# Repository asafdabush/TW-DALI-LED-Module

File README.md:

# TW DALI LED Module: Two-Channel Tunable-White Driver with Isolated DALI Interface

A Ø50 mm round control-and-driver module for tunable-white (TW) COB LEDs. It takes a 24 V constant-voltage supply, drives a warm and a cool LED channel with independent constant-current buck regulators, and is controlled over an optically isolated DALI bus by an STM32G0 microcontroller.

Personal hardware project, designed end to end in KiCad 9.

**Status:** schematic and 2-layer layout complete. Next steps are fabrication, bring-up and the DALI DT8 firmware.

---

Full schematic: [`docs/schematic.pdf`](docs/schematic.pdf)

## Architecture

```mermaid
flowchart LR
    V[24 V CV input] --> P[Protection<br/>SS34 reverse-polarity<br/>1.1 A PTC · SMBJ26A TVS]
    P --> REG[L78L33<br/>3.3 V]
    P --> CW[AL8860 buck<br/>cool channel]
    P --> WW[AL8860 buck<br/>warm channel]
    REG --> MCU[STM32G071KB]
    MCU -- PWM / DAC --> CW
    MCU -- PWM / DAC --> WW
    CW --> LC[COB cool]
    WW --> LW[COB warm]
    BUS[DALI bus] --- ISO[Isolated DALI PHY<br/>2× TCMT1107 opto]
    ISO -- RX / TX --> MCU
```

The board is split into two galvanically isolated domains: the 24 V power and MCU domain, and the DALI bus domain. The only link between them is the two optocouplers (3.75 kV rms).

## Design Blocks

### Power input

- **Reverse-polarity protection:** SS34 Schottky in series.
- **Overcurrent:** 1.1 A resettable PTC fuse.
- **Transient clamp:** SMBJ26A TVS across the 24 V rail.
- **Logic supply:** L78L33 linear regulator for the MCU only, so its dissipation stays small (≈ 20.7 V × ~10 mA ≈ 0.2 W).

### Constant-current LED channels (×2, one hierarchical sheet instantiated twice)

- **Topology:** AL8860 hysteretic buck with high-side current sensing, a 47 µH Bourns SRN6028 inductor and a PMEG4010 freewheel Schottky.
- **Output current:** set by the sense resistor, I_LED = V_SENSE / R_S = 0.1 V / 0.15 Ω ≈ **667 mA** per channel (nominal), with P_RS ≈ 67 mW.
- **Dimming:** the CTRL pin accepts either timer PWM directly, or an analog level from the MCU DAC through 1 kΩ. Firmware keeps whichever source is unused in high impedance. A 10 kΩ pull-down holds the LEDs off while the MCU is in reset.
- **Decoupling:** 4.7 µF + 100 nF / 50 V at each regulator input.

### Isolated DALI physical layer

- **Polarity-free bus connection:** MB6S bridge rectifier, with an SMBJ24A TVS across the bus.
- **Receive:** a BZX384-C5V1 Zener sets the detection threshold between DALI low (< 4.5 V) and high (> 9.5 V). The opto LED current is limited by a two-transistor current sink (BC847 pair, R = 680 Ω), so I ≈ V_BE / R ≈ 1 mA, inside the DALI 2 mA per-device budget. The receiver output is pulled up to 3.3 V, so the logic is inverted (bus idle-high gives RX low).
- **Transmit:** the MCU drives the TCMT1107 LED through 330 Ω (≈ 6 mA). The opto output pulls the gate of an AO3400A to the bus through 10 kΩ, and the MOSFET shorts the rectified bus to signal a logic low. A 10 V Zener clamps V_GS, and 100 kΩ keeps the gate off by default.

### Microcontroller

| Function | STM32G071KB pin |
|---|---|
| DALI RX / TX | PA0 / PA1 |
| PWM cool / warm | PA6 (TIM3_CH1) / PA3 (TIM2_CH4) |
| DAC cool / warm | PA5 (DAC1_OUT2) / PA4 (DAC1_OUT1) |
| Programming | SWD test pads: 3V3, SWDIO, SWCLK, NRST, GND |

## PCB

- Round Ø50 mm, 2 layers, 1.6 mm FR-4, two M3 mounting holes.
- An isolation barrier: a ~5 mm copper keep-out band across the board under the two optocouplers separates the 24 V/MCU domain from the DALI domain. The bottom-layer ground pour stays on the power side only.
- Wide traces (0.8 mm `Power` net class) for the 24 V rail and the LED current loops. The buck switching loops are kept tight around each AL8860, its inductor and its freewheel diode.
- Solder-wire pads for 24 V in, DALI, and the two COB channels.

## Repository Contents

| Path | Contents |
|---|---|
| [`docs/schematic.pdf`](docs/schematic.pdf) | Full schematic, 6 sheets |
| [`hardware/`](hardware) | KiCad 9 project: root sheet plus `power`, `led_channel` (×2), `mcu` and `dali` sub-sheets, and the PCB |
| [`docs/BOM.csv`](docs/BOM.csv) | Bill of materials (47 parts, 31 lines) |
| [`docs/pcb_top.png`](docs/pcb_top.png) | Layout render |

Open `hardware/TW_DALI_Module.kicad_pro` in KiCad 9 or later.

## Roadmap

- [ ] Fabricate and assemble the first batch
- [ ] Bring-up: verify 3.3 V rail, set-current accuracy, buck ripple and switching frequency at 24 V
- [ ] DALI PHY: verify the RX threshold and the TX timing (1200 bit/s Manchester) with a DALI master. The estimated bus-side threshold (Zener + opto LED + V_BE + bridge drops) is ≈ 8.5–9 V, so the margin to the 9.5 V high level needs to be measured
- [ ] Firmware: IEC 62386-102 control gear plus DT8 colour-temperature commands
- [ ] Thermal measurement at full load on both channels

## License

[CERN Open Hardware Licence v2 – Strongly Reciprocal](LICENSE)

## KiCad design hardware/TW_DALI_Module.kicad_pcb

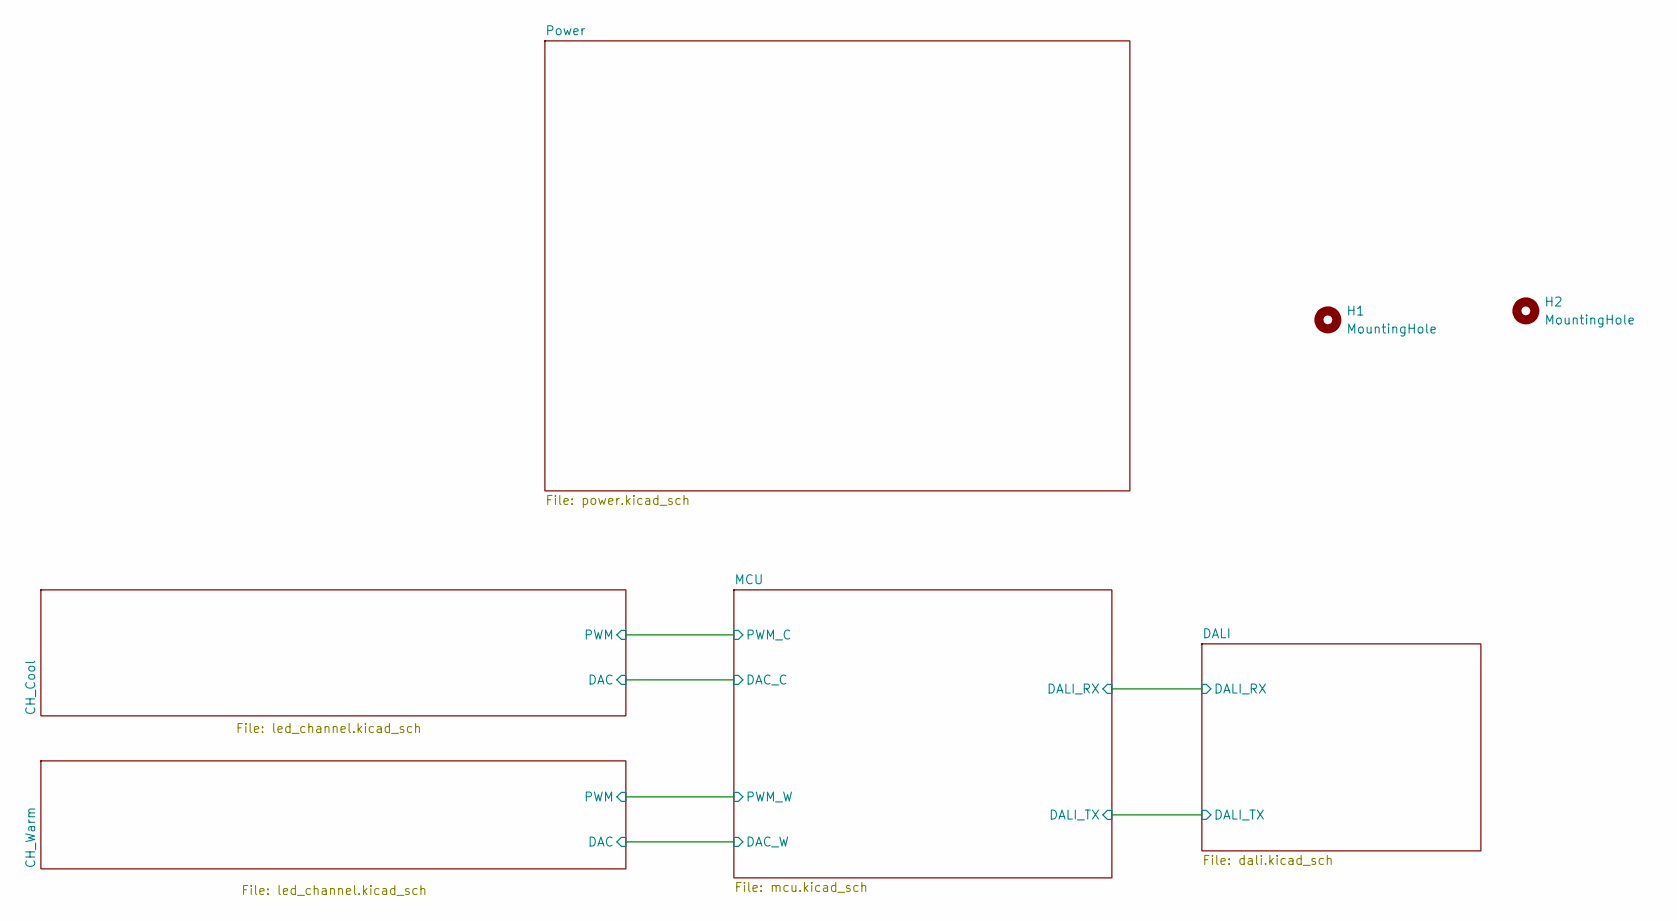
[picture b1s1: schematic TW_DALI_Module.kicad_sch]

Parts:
H1, H2: MountingHole; MountingHole_3.2mm_M3

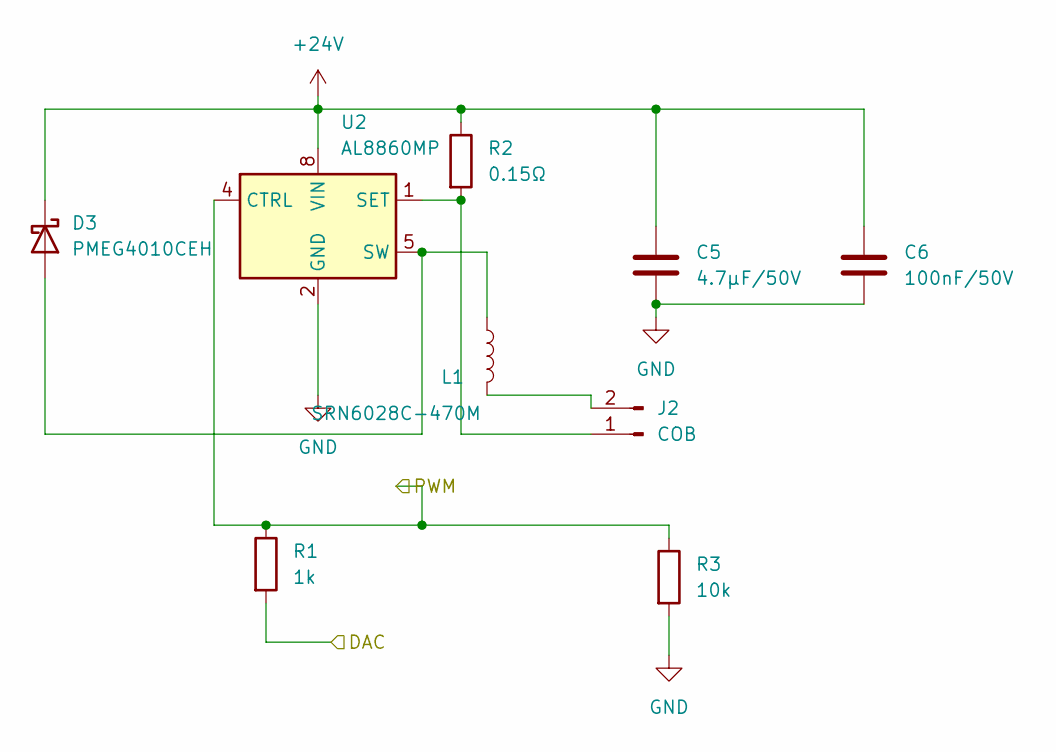
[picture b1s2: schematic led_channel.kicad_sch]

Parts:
C5: 4.7µF/50V; C_1206_3216Metric
C6: 100nF/50V; C_0603_1608Metric
D3: PMEG4010CEH; D_SOD-123F
J2: COB; SolderWire-0.5sqmm_1x02_P4.6mm_D0.9mm_OD2.1mm
L1: SRN6028C-470M; L_Bourns-SRN6028
R1: 1k; R_0603_1608Metric
R2: 0.15Ω; R_0805_2012Metric
R3: 10k; R_0603_1608Metric
U2: AL8860MP; MSOP-8-1EP_3x3mm_P0.65mm_EP1.5x1.8mm

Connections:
+24V: C5.1, C6.1, D3.1 (K), R2.1, U2.8 (VIN); also elsewhere on the board
/CH_Cool/DAC: R1.2; also elsewhere on the board
/CH_Cool/PWM: R1.1, R3.1, U2.4 (CTRL); also elsewhere on the board
GND: C5.2, C6.2, R3.2, U2.2 (GND), U2.3 (GND), U2.9 (GND); also elsewhere on the board
unnamed: D3.2 (A), L1.1, U2.5 (SW), U2.6 (SW)
unnamed: J2.1, R2.2, U2.1 (SET)
unnamed: J2.2, L1.2

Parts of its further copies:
C7: 4.7µF/50V; C_1206_3216Metric
C8: 100nF/50V; C_0603_1608Metric
D4: PMEG4010CEH; D_SOD-123F
J3: COB; SolderWire-0.5sqmm_1x02_P4.6mm_D0.9mm_OD2.1mm
L2: SRN6028C-470M; L_Bourns-SRN6028
R4: 1k; R_0603_1608Metric
R5: 0.15Ω; R_0805_2012Metric
R6: 10k; R_0603_1608Metric
U3: AL8860MP; MSOP-8-1EP_3x3mm_P0.65mm_EP1.5x1.8mm

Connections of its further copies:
+24V: C7.1, C8.1, D4.1 (K), R5.1, U3.8 (VIN); also elsewhere on the board
/CH_Warm/DAC: R4.2; also elsewhere on the board
/CH_Warm/PWM: R4.1, R6.1, U3.4 (CTRL); also elsewhere on the board
GND: C7.2, C8.2, R6.2, U3.2 (GND), U3.3 (GND), U3.9 (GND); also elsewhere on the board
unnamed: D4.2 (A), L2.1, U3.5 (SW), U3.6 (SW)
unnamed: J3.1, R5.2, U3.1 (SET)
unnamed: J3.2, L2.2

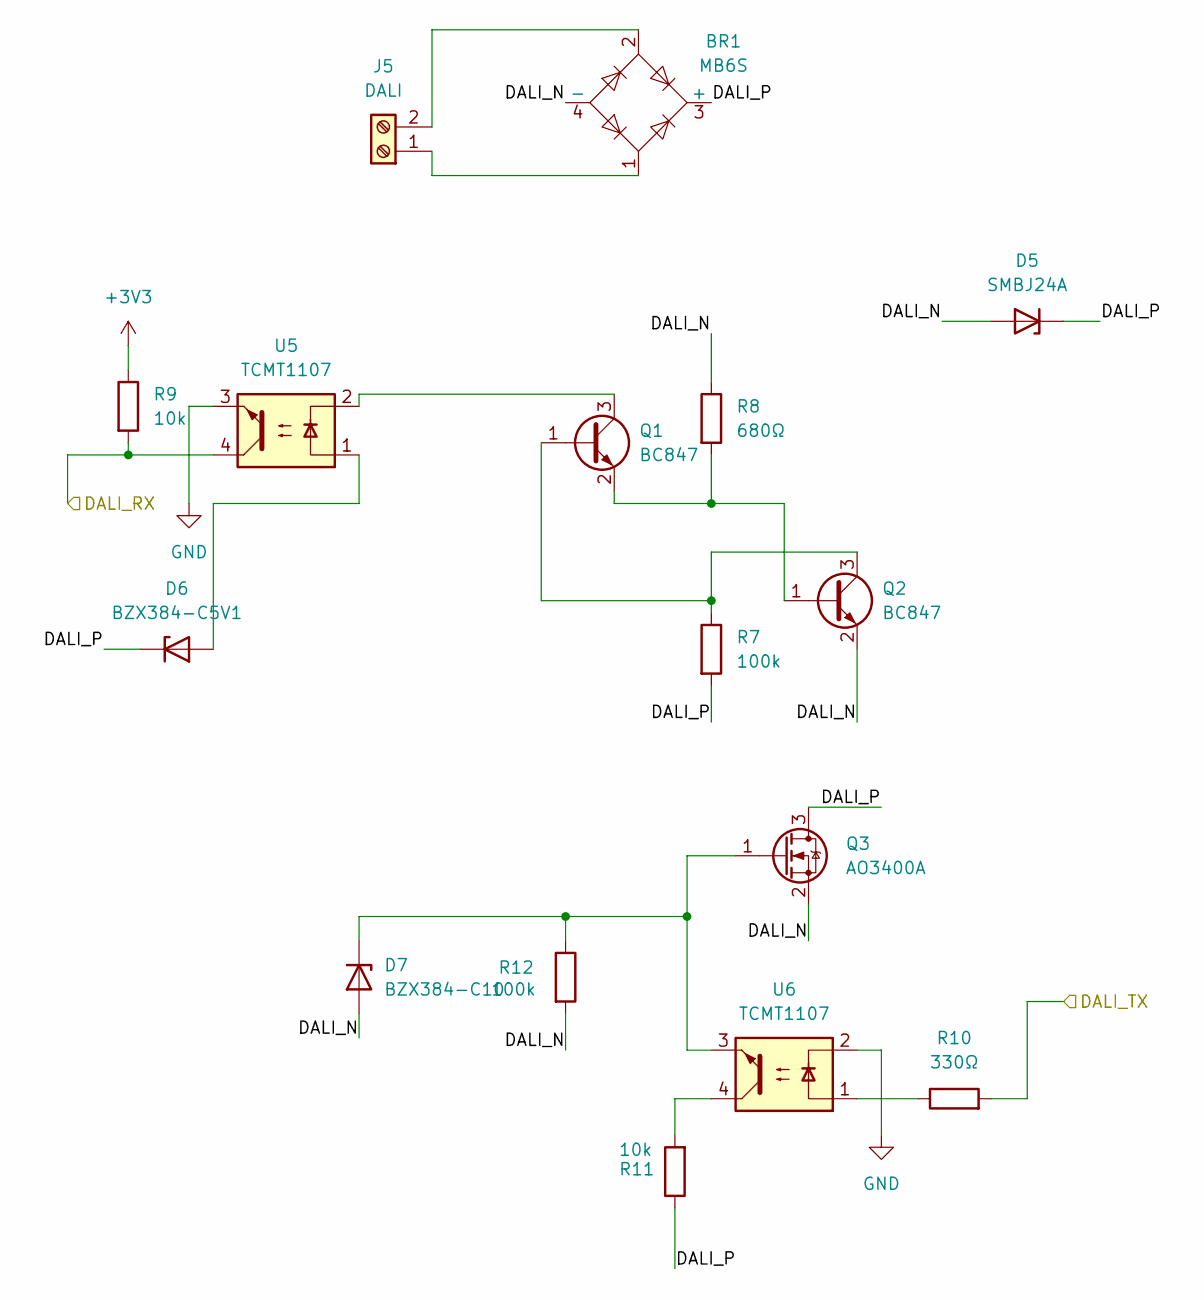
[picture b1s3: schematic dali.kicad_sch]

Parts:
BR1: MB6S; TO-269AA
D5: SMBJ24A; D_SMB
D6: BZX384-C5V1; D_SOD-323
D7: BZX384-C10; D_SOD-323
J5: DALI; SolderWire-0.5sqmm_1x02_P4.6mm_D0.9mm_OD2.1mm
Q1, Q2: BC847; SOT-23
Q3: AO3400A; SOT-23
R7, R12: 100k; R_0603_1608Metric
R8: 680Ω; R_0603_1608Metric
R9, R11: 10k; R_0603_1608Metric
R10: 330Ω; R_0603_1608Metric
U5, U6: TCMT1107; SOP-4_4.4x2.6mm_P1.27mm

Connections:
+3V3: R9.1; also elsewhere on the board
/DALI/DALI_N: BR1.4 (-), D5.2 (A), D7.2 (A), Q2.2 (E), Q3.2 (S), R8.1, R12.2
/DALI/DALI_P: BR1.3 (+), D5.1 (K), D6.1 (K), Q3.3 (D), R7.2, R11.1
/DALI/DALI_RX: R9.2, U5.4; also elsewhere on the board
/DALI/DALI_TX: R10.2; also elsewhere on the board
GND: U5.3, U6.2; also elsewhere on the board
unnamed: D6.2 (A), U5.1
unnamed: D7.1 (K), Q3.1 (G), R12.1, U6.3
unnamed: BR1.1, J5.1
unnamed: BR1.2, J5.2
unnamed: Q1.1 (B), Q2.3 (C), R7.1
unnamed: Q1.3 (C), U5.2
unnamed: Q1.2 (E), Q2.1 (B), R8.2
unnamed: R10.1, U6.1
unnamed: R11.2, U6.4

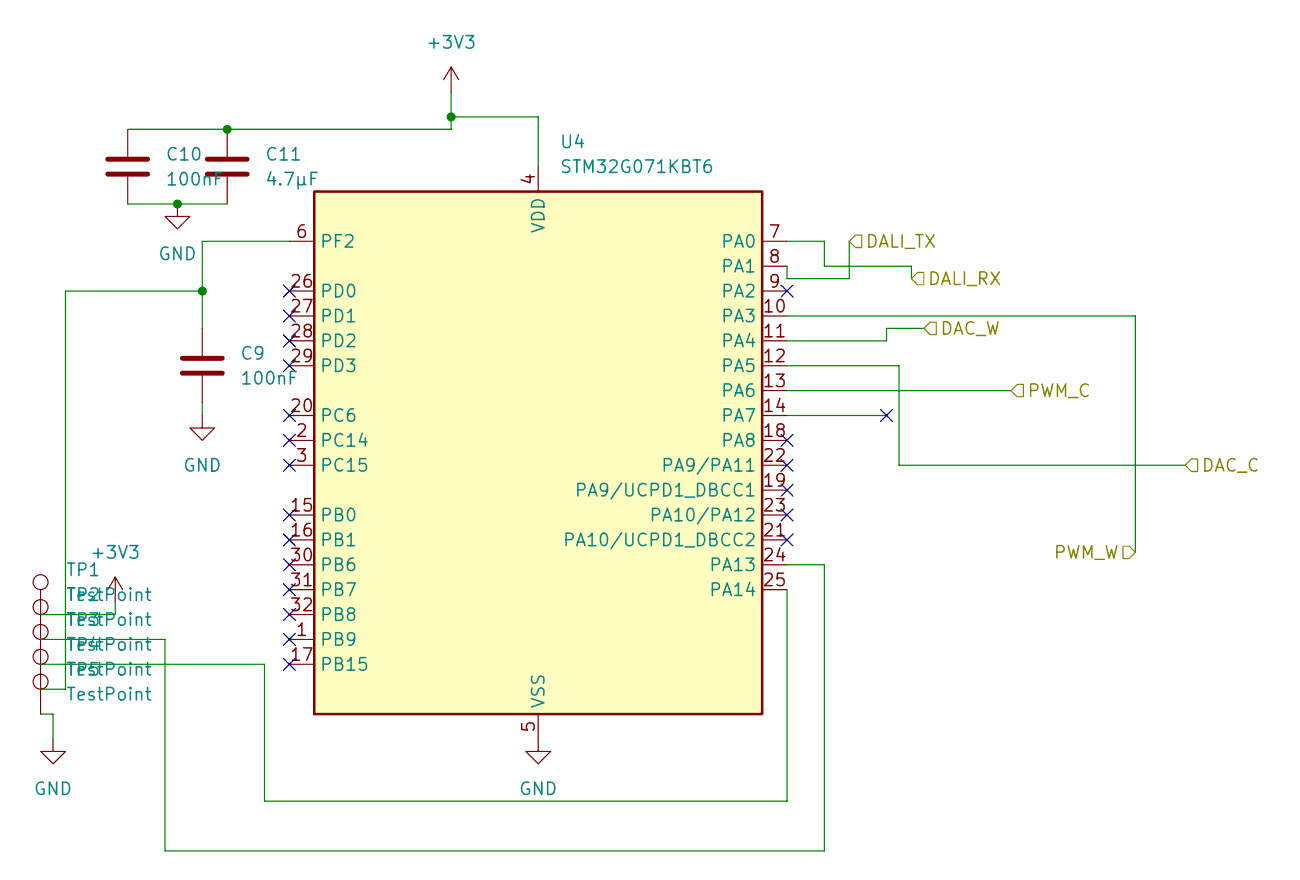
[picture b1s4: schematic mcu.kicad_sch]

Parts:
C9, C10: 100nF; C_0603_1608Metric
C11: 4.7µF; C_0603_1608Metric
TP1, TP2, TP3, TP4, TP5: TestPoint; TestPoint_Pad_D1.0mm
U4: STM32G071KBT6; LQFP-32_7x7mm_P0.8mm

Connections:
+3V3: C10.1, C11.1, TP1.1, U4.4 (VDD); also elsewhere on the board
/CH_Cool/DAC: U4.12 (PA5); also elsewhere on the board
/CH_Cool/PWM: U4.13 (PA6); also elsewhere on the board
/CH_Warm/DAC: U4.11 (PA4); also elsewhere on the board
/CH_Warm/PWM: U4.10 (PA3); also elsewhere on the board
/DALI/DALI_RX: U4.7 (PA0); also elsewhere on the board
/DALI/DALI_TX: U4.8 (PA1); also elsewhere on the board
GND: C9.2, C10.2, C11.2, TP5.1, U4.5 (VSS); also elsewhere on the board
unnamed: TP2.1, U4.24 (PA13)
unnamed: TP3.1, U4.25 (PA14)
unnamed: C9.1, TP4.1, U4.6 (PF2)

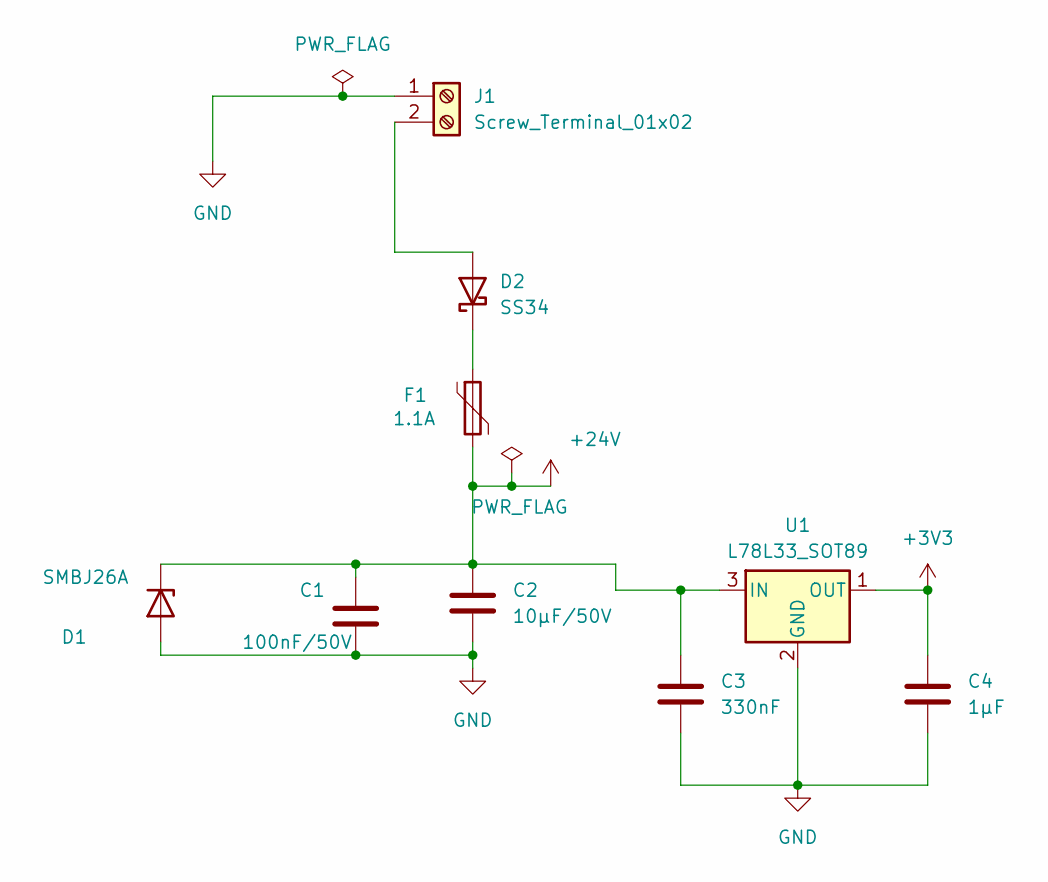
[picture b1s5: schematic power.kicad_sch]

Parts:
C1: 100nF/50V; C_0603_1608Metric
C2: 10µF/50V; C_1210_3225Metric
C3: 330nF; C_0603_1608Metric
C4: 1µF; C_0603_1608Metric
D1: SMBJ26A; D_SMB
D2: SS34; D_SMA
F1: 1.1A; Fuse_1206_3216Metric
J1: Screw_Terminal_01x02; SolderWire-0.5sqmm_1x02_P4.6mm_D0.9mm_OD2.1mm
U1: L78L33_SOT89; SOT-89-3

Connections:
+3V3: C4.1, U1.1 (OUT); also elsewhere on the board
+24V: C1.1, C2.1, C3.1, D1.1 (K), F1.2, U1.3 (IN); also elsewhere on the board
GND: C1.2, C2.2, C3.2, C4.2, D1.2 (A), J1.1, U1.2 (GND); also elsewhere on the board
unnamed: D2.2 (A), J1.2
unnamed: D2.1 (K), F1.1

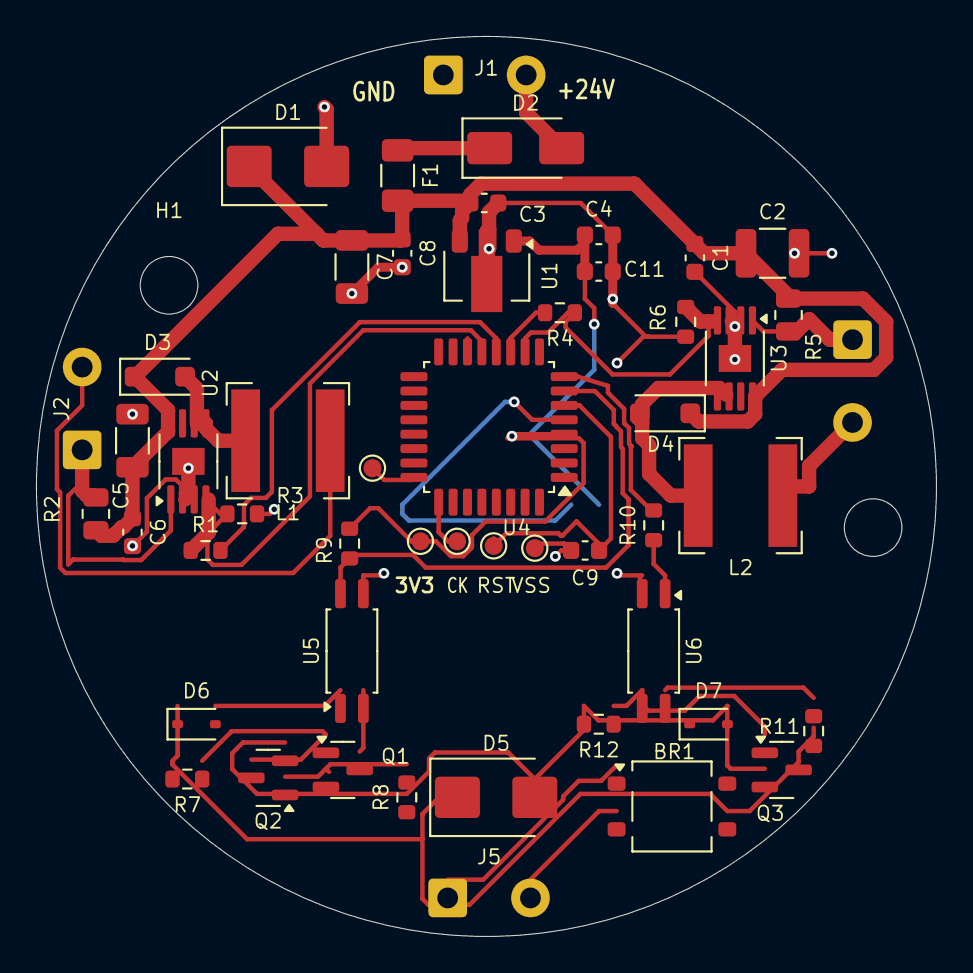
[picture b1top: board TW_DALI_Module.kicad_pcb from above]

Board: 2 copper layers, 50.0 x 50.0 mm, 54 parts (1 on the bottom side), 31 nets.

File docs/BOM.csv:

References,Qty,Value,Footprint
BR1,1,MB6S,TO-269AA
"C1, C6, C8",3,100nF/50V,C_0603_1608Metric
C2,1,10µF/50V,C_1210_3225Metric
C3,1,330nF,C_0603_1608Metric
C4,1,1µF,C_0603_1608Metric
"C5, C7",2,4.7µF/50V,C_1206_3216Metric
"C9, C10",2,100nF,C_0603_1608Metric
C11,1,4.7µF,C_0603_1608Metric
D1,1,SMBJ26A,D_SMB
D2,1,SS34,D_SMA
"D3, D4",2,PMEG4010CEH,D_SOD-123F
D5,1,SMBJ24A,D_SMB
D6,1,BZX384-C5V1,D_SOD-323
D7,1,BZX384-C10,D_SOD-323
F1,1,1.1A,Fuse_1206_3216Metric
J1,1,Screw_Terminal_01x02,SolderWire-0.5sqmm_1x02_P4.6mm_D0.9mm_OD2.1mm
"J2, J3",2,COB,SolderWire-0.5sqmm_1x02_P4.6mm_D0.9mm_OD2.1mm
J5,1,DALI,SolderWire-0.5sqmm_1x02_P4.6mm_D0.9mm_OD2.1mm
"L1, L2",2,SRN6028C-470M,L_Bourns-SRN6028
"Q1, Q2",2,BC847,SOT-23
Q3,1,AO3400A,SOT-23
"R1, R4",2,1k,R_0603_1608Metric
"R2, R5",2,0.15Ω,R_0805_2012Metric
"R3, R6, R9, R11",4,10k,R_0603_1608Metric
"R7, R12",2,100k,R_0603_1608Metric
R8,1,680Ω,R_0603_1608Metric
R10,1,330Ω,R_0603_1608Metric
U1,1,L78L33_SOT89,SOT-89-3
"U2, U3",2,AL8860MP,MSOP-8-1EP_3x3mm_P0.65mm_EP1.5x1.8mm
U4,1,STM32G071KBT6,LQFP-32_7x7mm_P0.8mm
"U5, U6",2,TCMT1107,SOP-4_4.4x2.6mm_P1.27mm
